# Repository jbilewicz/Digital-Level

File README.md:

#  Digital Level

## 📝 Project Overview
This project is a high-precision digital level based on the **ESP32** microcontroller. It utilizes the **MPU6050** 6-axis accelerometer and gyroscope to measure tilt angles in real-time. When the device reaches a perfectly horizontal position (tilt < 0.30 m/s² on X and Y axes), it triggers an audible alert.

##  Tech Stack

---

##  Components
- **Microcontroller:** ESP32 DEVKIT V1.
- **Sensor:** MPU6050 (Accelerometer & Gyroscope).
- **Display:** 0.96" SSD1306 OLED (128x64) via I2C.
- **Audio:** Active Buzzer for level notification.
- **Prototyping:** Universal Protoboard (THT).

---

##  Hardware Design & Pinout
The system is powered via USB (5V). Both the sensor and the display share the **I2C bus** (GPIO 21 and 22).

| Component | ESP32 Pin | Function |
| :--- | :--- | :--- |
| **MPU6050 SDA** | GPIO 21 | I2C Data  |
| **MPU6050 SCL** | GPIO 22 | I2C Clock  |
| **SSD1306 SDA** | GPIO 21 | I2C Data  |
| **SSD1306 SCL** | GPIO 22 | I2C Clock  |
| **Active Buzzer**| GPIO 13 | Level Alert (Inverted Logic)  |

---

##  Key Algorithms
1. **Level Detection:** The system monitors `acceleration.x` and `acceleration.y`. If both values fall below `LEVEL_THRESHOLD` (0.30), the device is considered level.
2. **Visual Feedback:** Large text (Size 3) displays X/Y acceleration values, and an "**>>OK<<**" message appears when level.
3. **Inverted Buzzer Logic:** The buzzer is activated by pulling the pin **LOW**.

---

##  Repository Structure
- `/Code` - Arduino/C++ source code (.ino).
- `/Docs` - Full technical report in PDF format.
- `/Images` - Photos of the soldered protoboard.

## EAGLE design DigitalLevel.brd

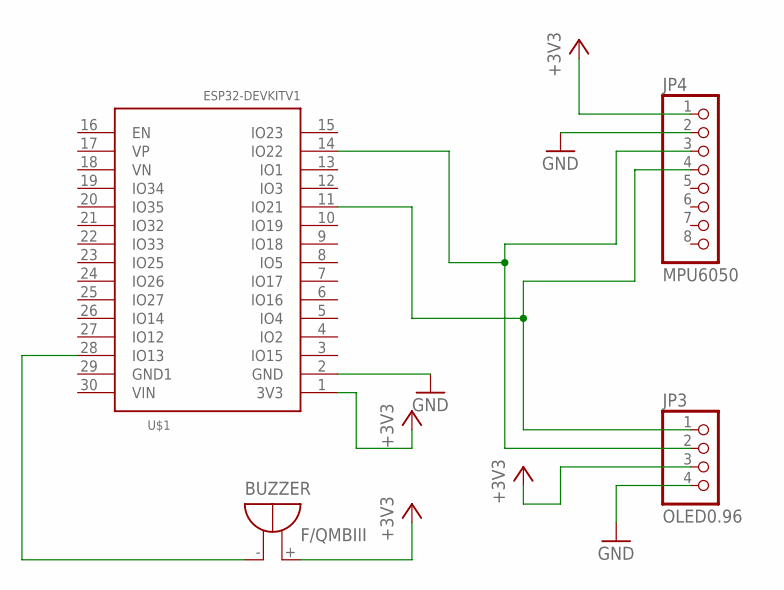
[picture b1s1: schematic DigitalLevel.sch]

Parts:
BUZZER: F/QMBIII
JP3: OLED0.96; 1X04
JP4: MPU6050; 1X08
U$1: ESP32DEVKITV1; ESP32-DEVKITV1

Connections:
+3V3: BUZZER.+ (-), JP3.3, JP4.1, U$1.1 (3V3)
GND: JP3.4, JP4.2, U$1.2 (GND)
unnamed: BUZZER.- (+), U$1.28 (IO13)
unnamed: JP3.1, JP4.4, U$1.11 (IO21)
unnamed: JP3.2, JP4.3, U$1.14 (IO22)

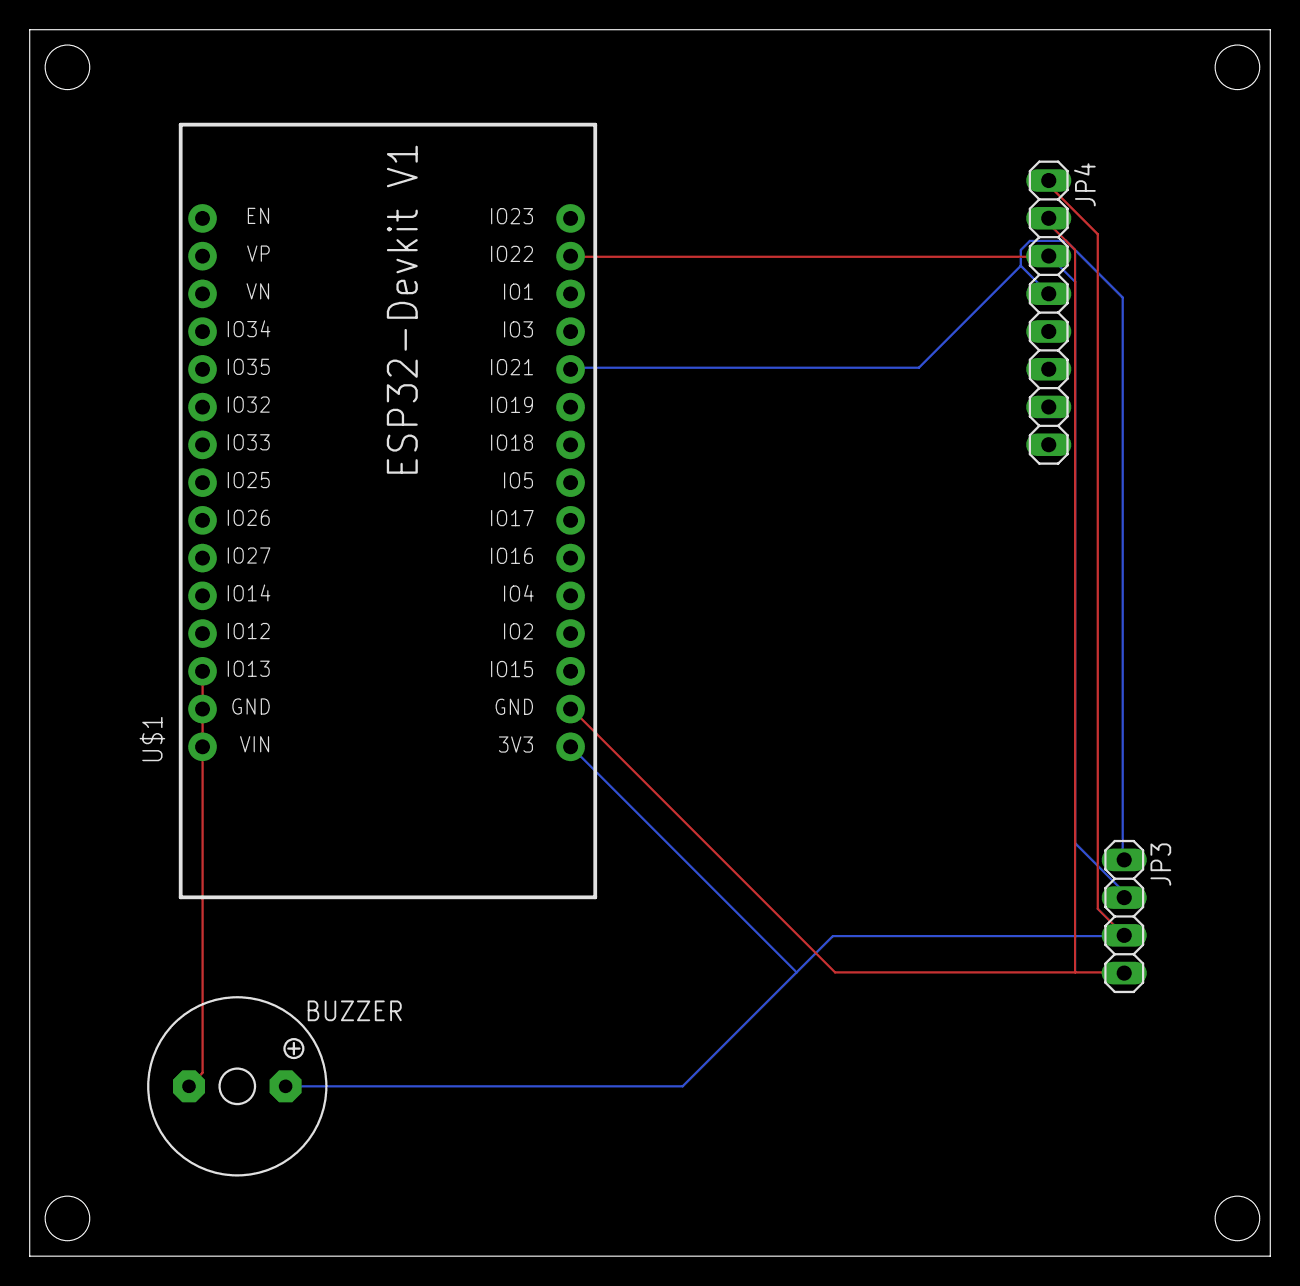
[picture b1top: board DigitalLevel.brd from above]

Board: 2 copper layers, 83.5 x 82.5 mm, 4 parts (0 on the bottom side), 5 nets.

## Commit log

2026-02-15 Enhance README with project details and structure
    Added detailed project overview, tech stack, components, hardware design, key algorithms, and repository structure to README.
2026-02-15 Fix formatting in project overview section
    Removed redundant citation start tag from project overview.
2026-02-15 Refactor README for clarity and readability
    Removed citation markers for clarity and improved readability.
2026-02-15 Remove contact information from README
    Removed contact information section from README.
2026-02-15 Update project title in README.md
    Removed the subtitle 'Poziomica Cyfrowa' from the project title.
